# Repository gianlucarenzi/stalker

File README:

README
------

This adapter can be used in the same time with an internal Amiga Keyboard
-------------------------------------------------------------------------

1- The reset key-combo are:
   LCTRL - LAMIGA - RAMIGA
   LCTRL - LALT   - DELETE

More can be used on demand.
--------------------------

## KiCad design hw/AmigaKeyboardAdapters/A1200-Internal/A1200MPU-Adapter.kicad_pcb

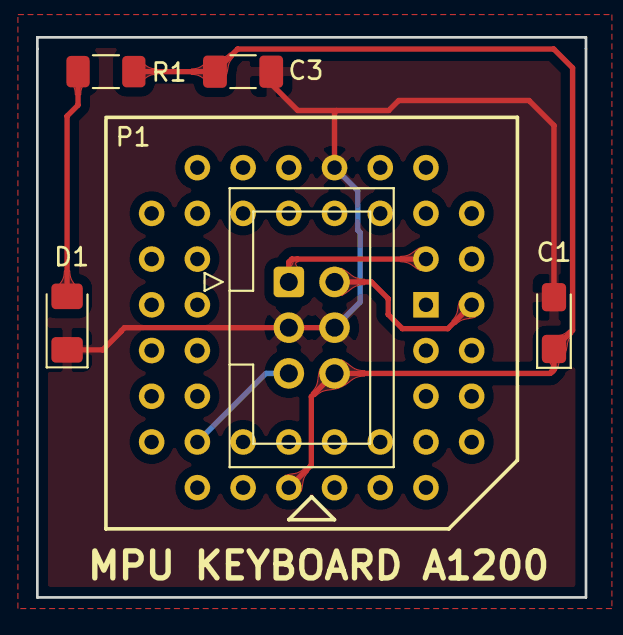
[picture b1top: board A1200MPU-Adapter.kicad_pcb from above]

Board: 2 copper layers, 30.5 x 31.1 mm, 6 parts (1 on the bottom side), 6 nets.

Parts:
C1: 10uF; CP_EIA-3216-12_Kemet-S_Pad1.58x1.35mm_HandSolder
C3: 100nF; C_1206_3216Metric_Pad1.33x1.80mm_HandSolder
D1: RED; LED_1206_3216Metric_Pad1.42x1.75mm_HandSolder
P1: Conn_02x03_Odd_Even; IDC-Header_2x03_P2.54mm_Vertical
R1: 330R; R_1206_3216Metric_Pad1.30x1.75mm_HandSolder
U1: A1200U13_REV_PLCC44; PLCC-44_THT-Socket_3D

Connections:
GND: C1.2, C3.2, D1.1, P1.3, P1.4, U1.35
unnamed: D1.2, R1.1
VCC5V: C1.1, C3.1, P1.6, R1.2, U1.13
mKBD_CLOCK: P1.1, U1.43
mKBD_DATA: P1.2, U1.44
mKBD_RESET: P1.5, U1.19

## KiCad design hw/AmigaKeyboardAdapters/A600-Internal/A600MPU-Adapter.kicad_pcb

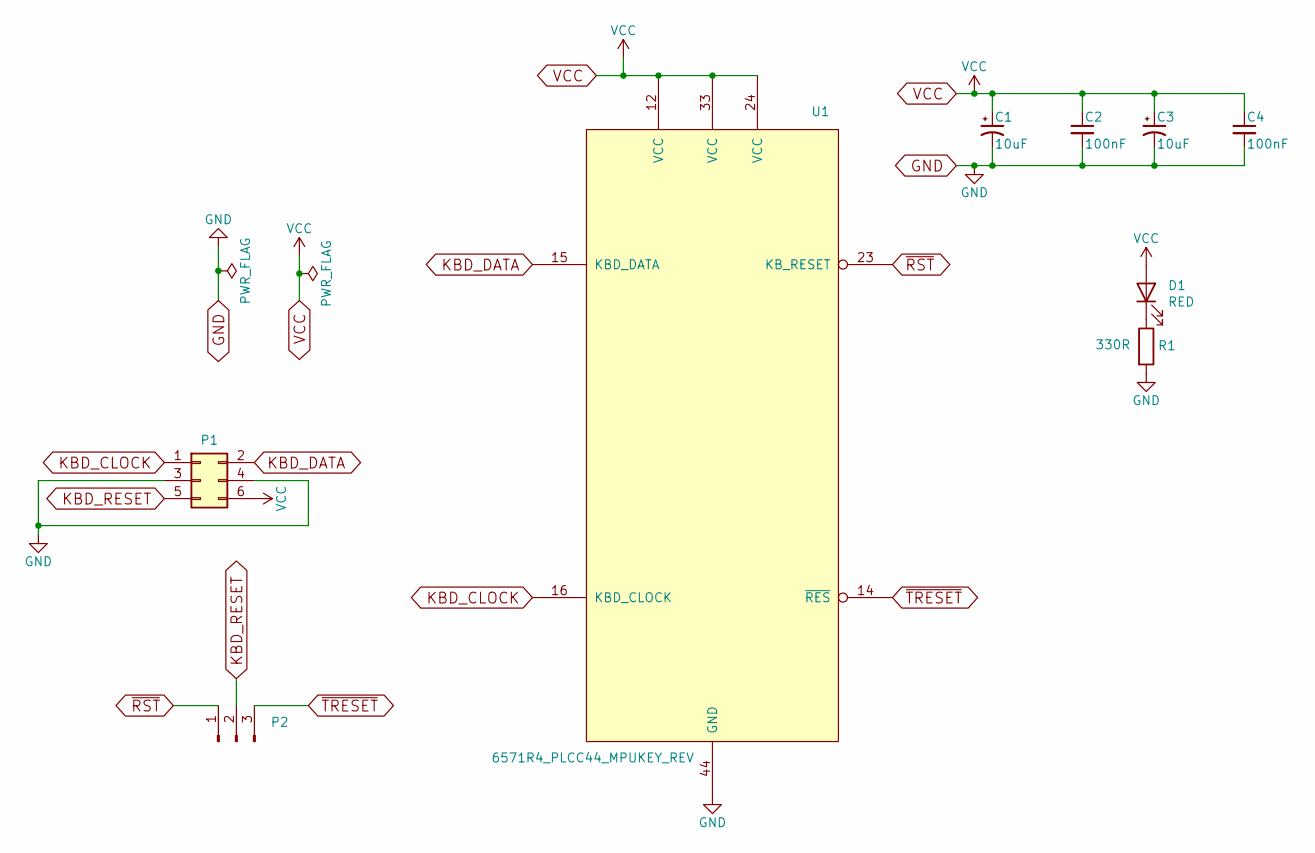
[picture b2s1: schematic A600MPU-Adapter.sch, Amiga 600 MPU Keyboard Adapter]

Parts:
C1, C3: 10uF; CP_EIA-3216-12_Kemet-S_Pad1.58x1.35mm_HandSolder; LCSC C108529
C2, C4: 100nF; C_1206_3216Metric_Pad1.33x1.80mm_HandSolder; LCSC C24497
D1: RED; LED_1206_3216Metric_Pad1.42x1.75mm_HandSolder; LCSC C93133
P1: Conn_02x03_Odd_Even; IDC-Header_2x03_P2.54mm_Vertical
P2: Conn_01x03_Male; PinHeader_1x03_P2.54mm_Vertical
R1: 330R; R_1206_3216Metric_Pad1.30x1.75mm_HandSolder; LCSC C245520
U1: 6571R4_PLCC44_MPUKEY_REV; PLCC-44_THT-Socket_3D

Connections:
GND: C1.2, C2.2, C3.2, C4.2, P1.3, P1.4, R1.2, U1.44 (GND)
KBD_CLOCK: P1.1, U1.16 (KBD_CLOCK)
KBD_DATA: P1.2, U1.15 (KBD_DATA)
KBD_RESET: P1.5, P2.2
unnamed: D1.1 (K), R1.1
VCC: C1.1, C2.1, C3.1, C4.1, D1.2 (A), P1.6, U1.12 (VCC), U1.24 (VCC), U1.33 (VCC)
~RST: P2.1, U1.23 (KB_RESET)
~TRESET: P2.3, U1.14 (~RES)

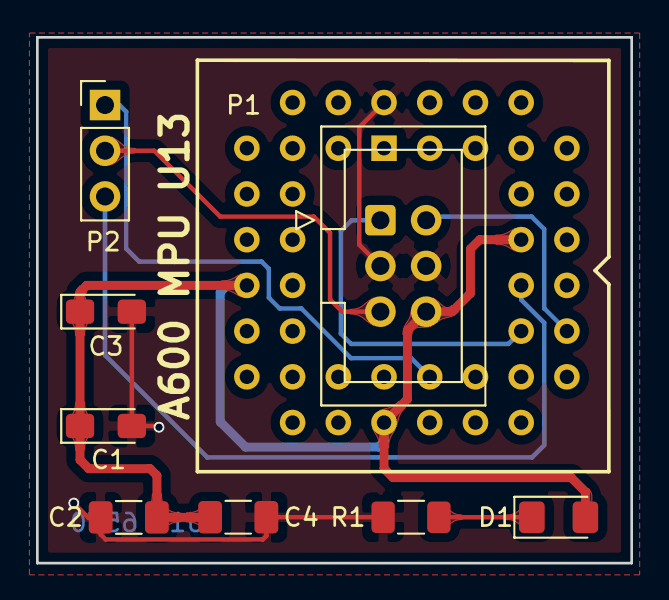
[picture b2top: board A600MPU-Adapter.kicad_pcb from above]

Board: 2 copper layers, 33.0 x 29.2 mm, 9 parts (1 on the bottom side), 8 nets.

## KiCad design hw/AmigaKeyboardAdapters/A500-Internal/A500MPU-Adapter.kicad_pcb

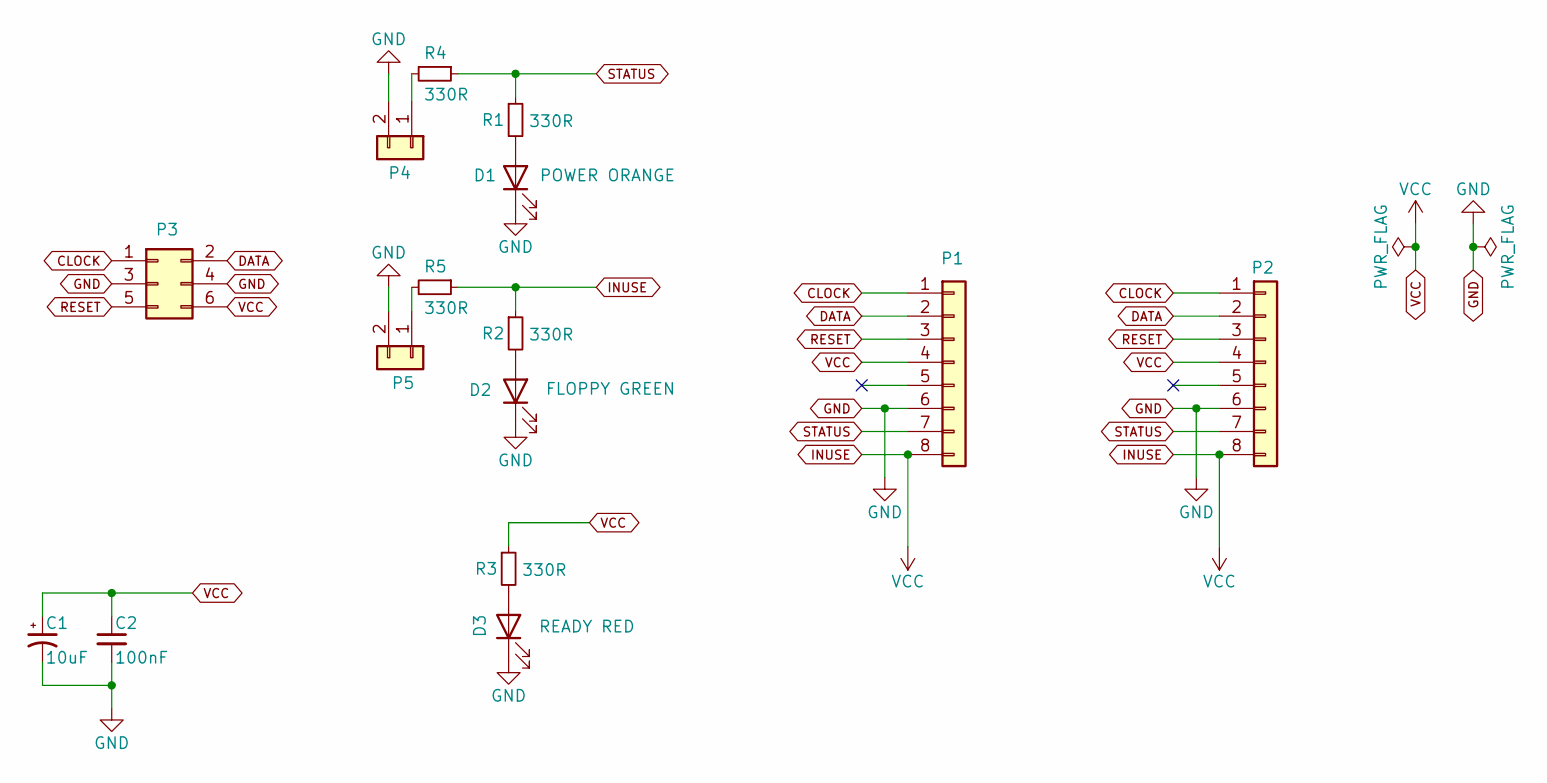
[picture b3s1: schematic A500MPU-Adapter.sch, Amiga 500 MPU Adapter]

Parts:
C1: 10uF; CP_EIA-3216-12_Kemet-S_Pad1.58x1.35mm_HandSolder; LCSC C108529
C2: 100nF; C_1206_3216Metric_Pad1.33x1.80mm_HandSolder; LCSC C24497
D1: POWER ORANGE; LED_1206_3216Metric_Pad1.42x1.75mm_HandSolder; LCSC C183851
D2: FLOPPY GREEN; LED_1206_3216Metric_Pad1.42x1.75mm_HandSolder; LCSC C2980185
D3: READY RED; LED_1206_3216Metric_Pad1.42x1.75mm_HandSolder; LCSC C93133
P1: Conn_01x08; PinHeader_1x08_P2.54mm_Vertical
P2: Conn_01x08; PinSocket_1x08_P2.54mm_Vertical
P3: Conn_02x03; IDC-Header_2x03_P2.54mm_Vertical
P4, P5: Conn_01x02; PinHeader_1x02_P2.54mm_Vertical
R1, R2, R3, R4, R5: 330R; R_1206_3216Metric_Pad1.30x1.75mm_HandSolder; LCSC C245520

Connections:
CLOCK: P1.1, P2.1, P3.1
DATA: P1.2, P2.2, P3.2
GND: C1.2, C2.2, D1.1 (K), D2.1 (K), D3.1 (K), P1.6, P2.6, P3.3, P3.4, P4.2, P5.2
INUSE: C1.1, C2.1, P1.4, P1.8, P2.4, P2.8, P3.6, R2.1, R3.1, R5.1
unnamed: D1.2 (A), R1.2
unnamed: D2.2 (A), R2.2
unnamed: D3.2 (A), R3.2
unnamed: P4.1, R4.2
unnamed: P5.1, R5.2
RESET: P1.3, P2.3, P3.5
STATUS: P1.7, P2.7, R1.1, R4.1

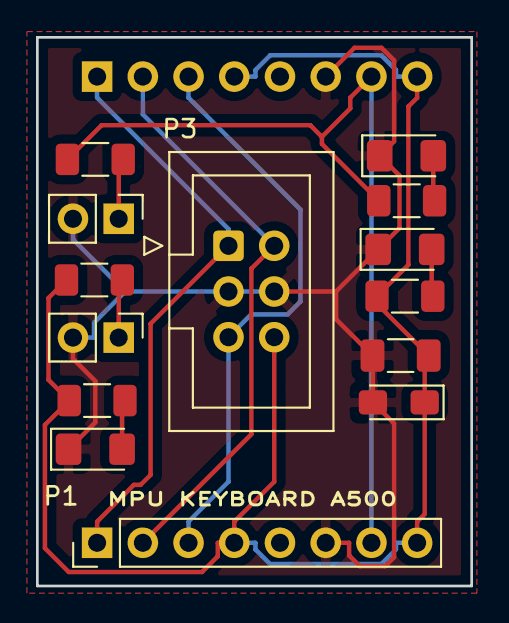
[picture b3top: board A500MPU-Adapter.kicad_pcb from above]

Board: 2 copper layers, 24.1 x 30.5 mm, 15 parts (1 on the bottom side), 11 nets.

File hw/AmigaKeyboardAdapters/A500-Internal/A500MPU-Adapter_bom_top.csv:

"Comment","Designator","Footprint","LCSC Part #"
"330R","R2 R3 R1 R4 R5","","C245520"
"100nF","C2","","C24497"
"10uF","C1","","C108529"
"Conn_02x03","P3","",""
"Conn_01x08","P1","",""
"Conn_01x02","P4 P5","",""
"FLOPPY GREEN","D2","","C2980185"
"READY RED","D3","","C93133"
"POWER ORANGE","D1","","C183851"

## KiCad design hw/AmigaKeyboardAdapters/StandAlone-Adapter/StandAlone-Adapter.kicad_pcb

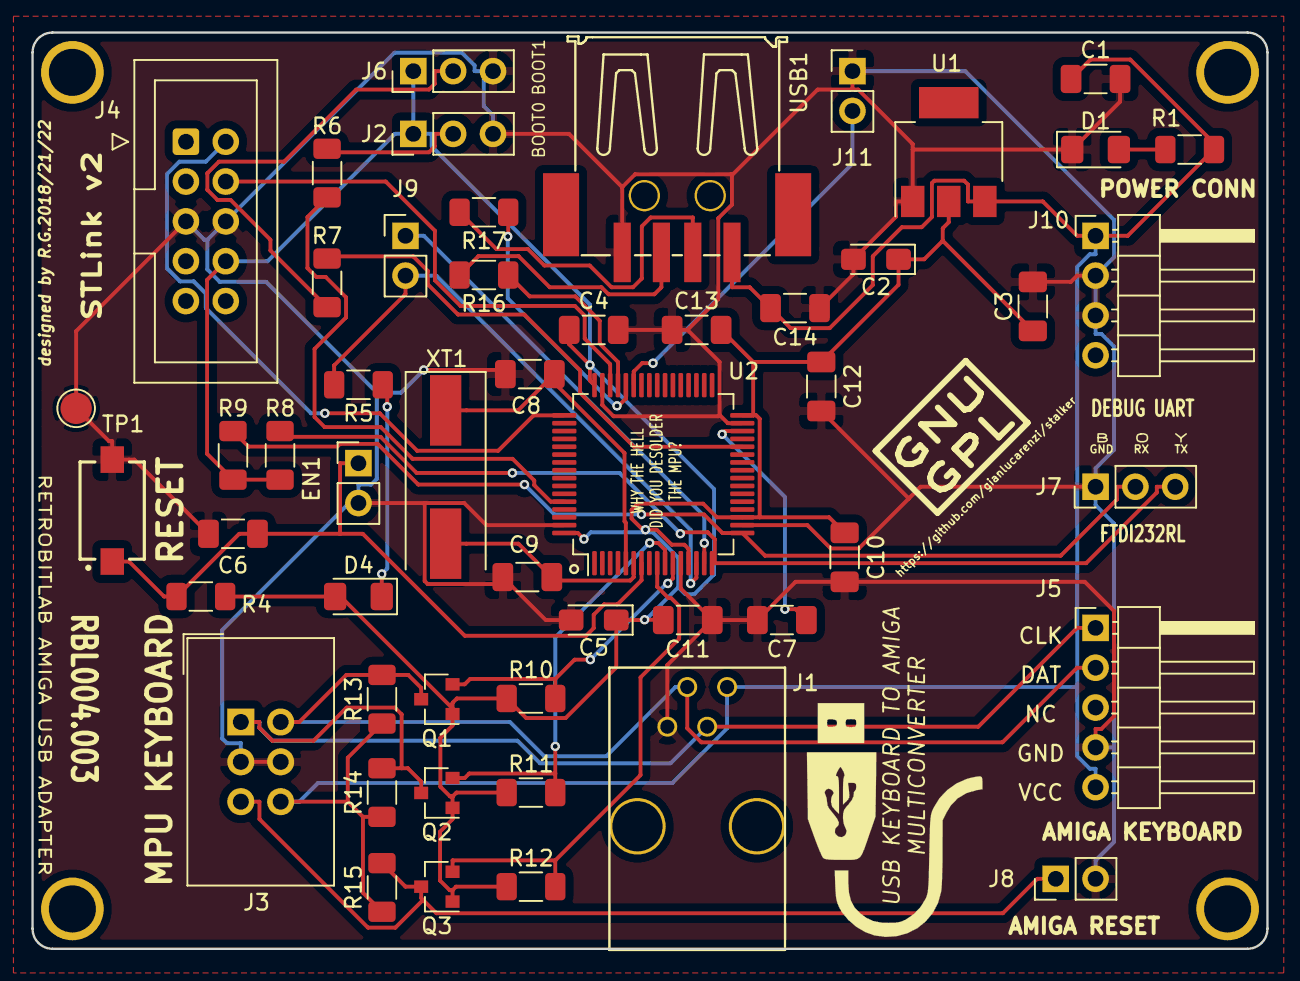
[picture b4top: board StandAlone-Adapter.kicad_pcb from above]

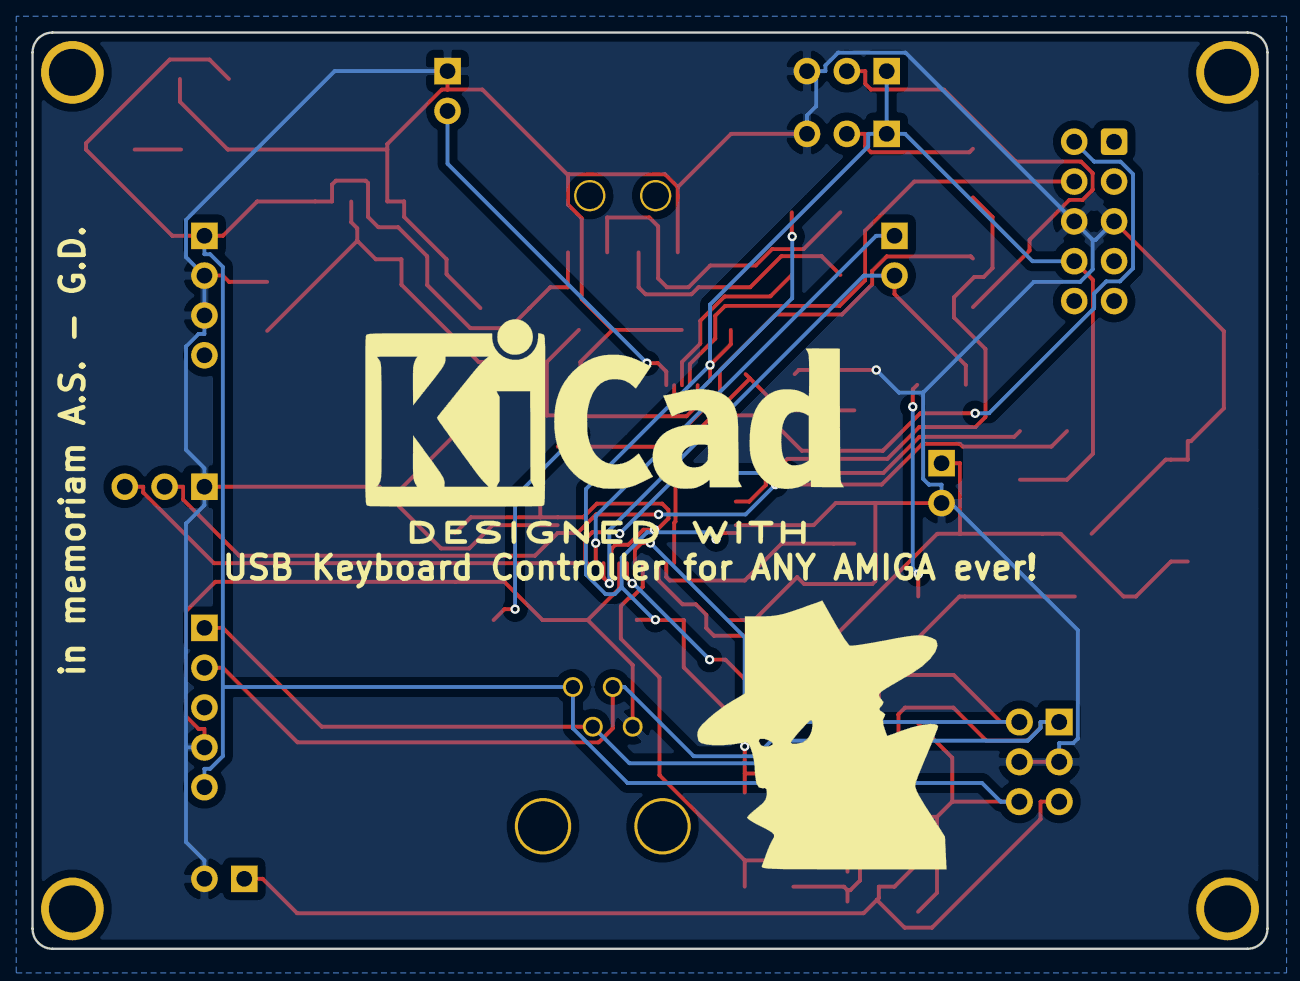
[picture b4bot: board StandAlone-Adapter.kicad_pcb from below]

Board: 2 copper layers, 78.7 x 58.4 mm, 60 parts (2 on the bottom side), 30 nets.

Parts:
C1: 100nF; C_1206_3216Metric_Pad1.33x1.80mm_HandSolder
C2: 10uF; CP_EIA-3216-12_Kemet-S_Pad1.58x1.35mm_HandSolder
C3, C4, C6, C10, C11, C12, C13, C14: 100n; C_1206_3216Metric_Pad1.33x1.80mm_HandSolder
C5: 10u; CP_EIA-3216-18_Kemet-A_Pad1.58x1.35mm_HandSolder
C7: 4.7uF; C_1206_3216Metric_Pad1.33x1.80mm_HandSolder
C8, C9: 22pF; C_1206_3216Metric_Pad1.33x1.80mm_HandSolder
D1, D4: RED; LED_1206_3216Metric_Pad1.42x1.75mm_HandSolder
EN1: CONN_01X02; PinHeader_1x02_P2.54mm_Vertical
H1, H2, H3, H4: CONN_01X01; MountingHole
J1: RJ10; RJ10-RECEPTACLE-Assmann-ASS-2004-3-4-LP-N-R
J2, J6, J7: Conn_01x03; PinHeader_1x03_P2.54mm_Vertical
J3: Conn_02x03_Odd_Even; IDC-Header_2x03_P2.54mm_Vertical
J4: JTAG SWDIO SWCLK; IDC-Header_2x05_P2.54mm_Vertical
J5: Conn_01x05; PinHeader_1x05_P2.54mm_Horizontal
J8, J9, J11: Conn_01x02; PinHeader_1x02_P2.54mm_Vertical
J10: Conn_01x04; PinHeader_1x04_P2.54mm_Horizontal
LOGO1: USB; USB_PLUG_15x15mm
LOGO2: GPL; KiCad-Logo2_12mm_SilkScreen
LOGO3: STALKER!; Symbol_GNU-GPL_SilkScreen_Small
LOGO4: Stalker Logo; Stalker_16.1x17.3mm
Q1, Q2, Q3: BSS138; SOT-23
R1, R5: 330R; R_1206_3216Metric_Pad1.30x1.75mm_HandSolder
R4, R6, R7, R8, R9, R10, R11, R12, R13, R14, R15: 10K; R_1206_3216Metric_Pad1.30x1.75mm_HandSolder
R16, R17: 22R; R_1206_3216Metric_Pad1.30x1.75mm_HandSolder
RESET1: SW_PUSH; SPST-7.3x3.9x2.5-WUERTH-434121025816
TP1: GND; TestPoint_Pad_D2.0mm
U1: AZ1117-3.3; SOT-223
U2: STM32F401RBTx; LQFP-64_10x10mm_P0.5mm
USB1: USB_A_SMD_LCSC; USB_A_M04P-F000_LCSC_C386738
XT1: 8Mhz; Crystal_SMD_HC49-SD

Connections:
+5V: C1.1, C14.2, J1.1, J3.6, J5.5, J10.1, R1.1, R13.1, R14.1, R15.1, U1.3, USB1.1
BOOT0: J2.2, R6.2
BOOT1: J6.2, R7.1
GND: C1.2, C2.2, C3.2, C4.2, C5.2, C6.1, C7.2, C8.2, C9.2, C10.1, C11.1, C12.1, C13.1, C14.1, D1.1, EN1.2, J1.4, J2.3, J3.3, J3.4, J4.5, J4.6, J5.4, J6.3, J7.1, J8.2, J10.2, J10.3, J11.1, RESET1.2, TP1.1, U1.1, U2.12, U2.18, U2.31, U2.47, U2.63, USB1.4
KBD_3v3_CLOCK: Q2.2, R11.2, U2.10
KBD_3v3_DATA: Q1.2, R10.2, U2.11
KBD_3v3_RESET: Q3.2, R12.2, U2.9
KBD_CLOCK: J1.2, J3.1, J5.1, Q2.3, R14.2
KBD_DATA: J1.3, J3.2, J5.2, Q1.3, R13.2
KBD_RESET: J3.5, J8.1, Q3.3, R15.2
NRST: C6.2, EN1.1, R4.1, RESET1.1, U2.7
unnamed: C7.1, U2.30
unnamed: C8.1, U2.5, XT1.1
unnamed: C9.1, U2.6, XT1.2
unnamed: D1.2, R1.2
unnamed: D4.1, R5.1
unnamed: R6.1, U2.60
unnamed: R7.2, U2.28
unnamed: R16.2, USB1.3
unnamed: R17.2, USB1.2
SWDCLK: J4.2, U2.49
SWDIO: J4.4, U2.46
TP1: J9.2, R5.2, U2.14
TP2: J9.1, U2.15
UART_RX_TTL: J7.2, R9.2, U2.17
UART_TX_TTL: J7.3, R8.2, U2.16
USB_ID: J11.2, U2.43
USB_N: R17.1, U2.44
USB_P: R16.1, U2.45
VCC3V3: C2.1, C3.1, C4.1, C5.1, C10.2, C11.2, C12.2, C13.2, D4.2, J2.1, J4.8, J6.1, Q1.1, Q2.1, Q3.1, R4.2, R8.1, R9.1, R10.1, R11.1, R12.1, U1.2, U2.13, U2.19, U2.32, U2.48, U2.64

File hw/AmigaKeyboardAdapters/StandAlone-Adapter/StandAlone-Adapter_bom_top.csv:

"Id";"Designator";"Package";"Quantity";"Designation";"Supplier and ref";
1;"C2";"CP_EIA-3216-12_Kemet-S_Pad1.58x1.35mm_HandSolder";1;"10uF";;;
2;"C3,C4,C6,C10,C11,C12,C13,C14";"C_1206_3216Metric_Pad1.33x1.80mm_HandSolder";8;"100n";;;
3;"C5";"CP_EIA-3216-18_Kemet-A_Pad1.58x1.35mm_HandSolder";1;"10u";;;
4;"C7";"C_1206_3216Metric_Pad1.33x1.80mm_HandSolder";1;"4.7uF";;;
5;"C8,C9";"C_1206_3216Metric_Pad1.33x1.80mm_HandSolder";2;"22pF";;;
6;"D1,D4";"LED_1206_3216Metric_Pad1.42x1.75mm_HandSolder";2;"RED";;;
7;"EN1";"PinHeader_1x02_P2.54mm_Vertical";1;"CONN_01X02";;;
8;"H1,H2,H3,H4";"MountingHole";4;"CONN_01X01";;;
9;"J1";"RJ10-RECEPTACLE-Assmann-ASS-2004-3-4-LP-N-R";1;"RJ10";;;
10;"J2,J6,J7";"PinHeader_1x03_P2.54mm_Vertical";3;"Conn_01x03";;;
11;"J3";"IDC-Header_2x03_P2.54mm_Vertical";1;"Conn_02x03_Odd_Even";;;
12;"J4,J10";"PinHeader_1x04_P2.54mm_Horizontal";2;"Conn_01x04";;;
13;"J5";"PinHeader_1x05_P2.54mm_Horizontal";1;"Conn_01x05";;;
14;"J8,J9,J11";"PinHeader_1x02_P2.54mm_Vertical";3;"Conn_01x02";;;
15;"Q1,Q2,Q3";"SOT-23";3;"BSS138";;;
16;"R1,R5";"R_1206_3216Metric_Pad1.30x1.75mm_HandSolder";2;"330R";;;
17;"R4,R6,R7,R8,R9,R10,R11,R12,R13,R14,R15";"R_1206_3216Metric_Pad1.30x1.75mm_HandSolder";11;"10K";;;
18;"R16,R17";"R_1206_3216Metric_Pad1.30x1.75mm_HandSolder";2;"22R";;;
19;"TP1";"TestPoint_Pad_D2.0mm";1;"GND";;;
20;"U1";"SOT-223";1;"AZ1117-3.3";;;
21;"U2";"LQFP-64_10x10mm_P0.5mm";1;"STM32F401RBTx";;;
22;"LOGO1";"USB_PLUG_15x15mm";1;"USB";;;
23;"LOGO2";"KiCad-Logo2_12mm_SilkScreen";1;"GPL";;;
24;"LOGO3";"Symbol_GNU-GPL_SilkScreen_Small";1;"STALKER!";;;
25;"LOGO4";"Stalker_16.1x17.3mm";1;"Stalker Logo";;;
26;"C1";"C_1206_3216Metric_Pad1.33x1.80mm_HandSolder";1;"100nF";;;
27;"RESET1";"SPST-7.3x3.9x2.5-WUERTH-434121025816";1;"SW_PUSH";;;
28;"XT1";"Crystal_SMD_HC49-SD";1;"8Mhz";;;
29;"USB1";"USB_A_M04P-F000_LCSC_C386738";1;"USB_A_SMD_LCSC";;;

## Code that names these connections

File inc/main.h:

/* USER CODE BEGIN Header */
/**
  ******************************************************************************
  * @file           : main.h
  * @brief          : Header for main.c file.
  *                   This file contains the common defines of the application.
  ******************************************************************************
  * @attention
  *
  * Copyright (c) 2025 STMicroelectronics.
  * All rights reserved.
  *
  * This software is licensed under terms that can be found in the LICENSE file
  * in the root directory of this software component.
  * If no LICENSE file comes with this software, it is provided AS-IS.
  *
  ******************************************************************************
  */
/* USER CODE END Header */

/* Define to prevent recursive inclusion -------------------------------------*/
#ifndef __MAIN_H
#define __MAIN_H

#define KBD_CLOCK_Pin       GPIO_PIN_2
#define KBD_CLOCK_GPIO_Port GPIOC
#define KBD_DATA_Pin        GPIO_PIN_3
#define KBD_DATA_GPIO_Port  GPIOC
#define KBD_RESET_Pin       GPIO_PIN_1
#define KBD_RESET_GPIO_Port GPIOC
#define TP1_Pin             GPIO_PIN_0
#define TP1_GPIO_Port       GPIOA
#define TP2_Pin             GPIO_PIN_1
#define TP2_GPIO_Port       GPIOA
#define LED_PIN_Pin         TP1_Pin
#define LED_PIN_GPIO_Port   TP1_GPIO_Port
#define DEBUG_TX_Pin        GPIO_PIN_2
#define DEBUG_TX_GPIO_Port  GPIOA
#define DEBUG_RX_Pin        GPIO_PIN_3
#define DEBUG_RX_GPIO_Port  GPIOA
#define USB_DM_Pin          GPIO_PIN_11
#define USB_DM_GPIO_Port    GPIOA
#define USB_DP_Pin          GPIO_PIN_12
#define USB_DP_GPIO_Port    GPIOA
#define USBH_Port           GPIOA

#ifdef __cplusplus
extern "C" {
#endif

/* Includes ------------------------------------------------------------------*/
#include "stm32f4xx_hal.h"

/* Private includes ----------------------------------------------------------*/
/* USER CODE BEGIN Includes */

/* USER CODE END Includes */

/* Exported types ------------------------------------------------------------*/
/* USER CODE BEGIN ET */

/* USER CODE END ET */

/* Exported constants --------------------------------------------------------*/
/* USER CODE BEGIN EC */

/* USER CODE END EC */

/* Exported macro ------------------------------------------------------------*/
/* USER CODE BEGIN EM */

/* USER CODE END EM */

/* Exported functions prototypes ---------------------------------------------*/
void Error_Handler(void);

/* USER CODE BEGIN EFP */

/* USER CODE END EFP */

/* Private defines -----------------------------------------------------------*/

/* USER CODE BEGIN Private defines */

/* USER CODE END Private defines */

#ifdef __cplusplus
}
#endif

#endif /* __MAIN_H */

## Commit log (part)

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2019-03-01 added the idc 2x3 box
2019-03-31 REfactoring for new Crystal Oscillator & new 1208 footprints handsoldering
2019-03-31 Bill Of Material Added
2019-03-31 Added Mouser's Bill of Material for 10 pcs. Just for reference for prices.
2019-04-01 Modified for better prices (10 pcs)
2019-04-05 removed. Must be reinstalled with the correctness of the files.
2019-04-12 Hide the LOGO label REF** on SilkScreen
2019-04-14 Modified for Capacitors & Added some boot options
    Replaced Electrolitic Capacitors with Tantalum ones. Added some
    capacitor as in the evaluation board schematics. Added BOOT1 pin. Added
    resistors for USB D+ D- lines. Increased the GND trace size to 0.35.
2019-04-18 Modified some logo and silkscreen stuff
2019-04-18 Added GNU GPL LOGO on silkscreen top
2019-04-18 Changed the capacitors for Crystal Oscillator. From 22pf to 20pf for 8Mhz
2019-04-22 Hide GNU LOGO Text
2019-06-05 Better optimization on release
2019-06-05 Better optimization on releaseAdded for gdb debug purposes
2019-06-17 Added the single-board Bill-Of-Material from DigiKey.
2019-06-17 Removed
2019-06-17 Removed unused Library (Memory Controller)
2019-06-22 KEYBOARD LED are in a binary format not decimal (each bit represent each led)
2019-06-22 Optimized even more (O3)
2019-06-22 Added SCROLL LOCK management
2019-06-22 Corrected. I do not have time to check what is really changed
2019-06-22 It works better with timed sync. Otherwise I have to rewrite the scan logic. BE CAREFUL: When using an internal keyboard and a USB keyboard, the logic with led for caps lock, scroll lock, and num loc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
2019-06-22 Rewrite of the lock mechanism. 1- The first press of a lock key (CAPS LOCK, NUM LOCK or SCROLL LOCK) send a _LOCK keycode to the system and lite up the corresponding led. 2- The following 'RELEASE' s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
    Works in Amiga 500 for now.
2019-06-22 Added check for reset when idle...
2019-06-22 Added a check for CLOCK line for external reset. 500msec of low means RESET!
2019-06-22 Corrected comment
2019-06-26 Updated silkscreen
2019-07-02 Changed comments to english
2019-09-07 Modified footprint of RJ10 (it was reversed)
2019-09-14 Revert "Modified footprint of RJ10 (it was reversed)"
    This reverts commit 65f5b3a9598e76c611fb4c453a8e3fe395b7212b.
2019-09-14 Added new images
2021-04-16 Modified for 128K as the STM32F401 with 128K is more common these days
2021-04-16 build folder is ignored
2021-04-16 From Kicad 4 to Kicad 5 update
2021-04-16 From Kicad 4 to Kicad 5
2022-05-25 Added DEBUG messages
2022-05-25 Added debug message
2022-10-13 Added a configuration for Amiga Reset. We can have a lot of Amiga reset keystrokes! LCTRL + LAMIGA + RAMIGA (standard) [ LGUI + RGUI ] LCTRL + LALT + RALT LCRTL + LALT + DEL (PC Standard) LCTRL + RAL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
2022-11-02 Removed Amiga (C)opyrighted stuff
2022-11-02 Rigenerated
2022-11-02 JLCPCB CPL
2022-11-04 Modifed project name
2022-11-04 Updated table for USB SCANCODES to AMIGA SCANCODES using: https://wiki.amigaos.net/wiki/Keymap_Library Added LCTRL for RESET checking
2022-11-05 Added 3D object for mechanical design
2022-11-07 Updated table. Added all Control keys (left and right)
2022-11-07 All components are SMD for a easier PCB production (LCSC and others) The jumper headers are optionals, so it will be soldered if needed. The programming tool STLINK_V2 will have a special programming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
2022-11-08 Done with bom2grouped_csv_jlcpcb.xsl
2022-11-08 Done by KiJLC plugin of PCBNEW
2022-11-08 MacOS ignore files
2022-11-09 Downloaded from LCSC
2022-11-09 Modified the JTAG STLinkV2 programmer port & SMT USB Type A connector
2022-11-10 For Autogeneration Routing (Kicad 5)
2022-11-10 For JLCPCB and LCSC Production
2022-11-10 Ignore cache lib files
2022-11-11 Updated to latest version (SMT - JLCPCB & LCSC Production run)
2022-11-14 First import. Must be adapted
2022-11-15 Added comments and swap tabs with spaces
2022-11-16 First try to autoproduce the bootloader
2022-11-16 No usb in this bootloader (it will be done in DFU)
2022-11-16 Modified for usage of only UART, GPIO. No more USB (it will be used inside the DFU mode)
2022-11-16 Ignore bootloader's build
2022-11-17 Sanity check added.
2022-11-29 Updated PWR_FLAGs
2022-11-29 New rendered images
2022-11-29 Updated PWR_FLAGs and other symbols
2022-11-30 Gerber for JLCPCB/PCBWay Production run
2022-11-30 Generated
2022-11-30 Generated for TOP & BOTTOM placement
2022-12-07 Smaller D1 silkscreen reference
2023-01-21 less verbose
2023-01-22 Removed unused macro
2023-01-22 Now flash.sh can be used to flash every firmware needed
2023-01-22 The application flash address space starts 0x4000 (16K) ahead of the bootloader, so the maximum amount of flash for application decrease from 128K to 112K
2023-01-22 Added NOISY output for debugging purposes
2023-02-11 Updated for a delayed USB init
2023-02-11 The SCB->VTOR has to be adapted for bootloader
2023-02-11 Adapter for bootloader (now 32K)
2023-02-11 First run
2023-02-11 Not needed but it is better to have
2023-02-13 Reduced Bootloader size to (hopefully) 16K
2023-02-13 Better calculation for size and start address
2023-02-15 Official release v1.2. Compiled without __EASTER_EGG__
2023-02-15 Modified RCC HSE setup as the CubeMX seems to have a bug, when calculating the clock resources the very first time. Change some of the divisors and resolve-the-issue works. :-/ It (should) works with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
    dfu-util --download build/stm32f401-usb-keyboard-amiga.bin --alt 0 --dfuse-address 0x08004000
    If does not work, change --alt 0 up to the numbers the system will gives you when invoking with --list option.
2023-02-18 Usage of the __appflash_start address (defined by the GNU linker script)
2023-02-18 Definition of the __appflash_start address for Application Start Address defined in the GNU linker script
2023-02-18 Change the linkerscript and the SCB->VTOR setting using the __appflash_start variable defined in the GNU linker script
2023-02-18 Usage of the __bootflash_start address (defined by the GNU linker script)
2023-02-18 Added #define DEBUG on DEBUG compiling: make DEBUG=1
2023-02-18 /* Prototypes */
2023-02-18 Added all symbols defined by the GNU linker script
2023-02-18 FWVER: v1.3 BUILD: 15:15:43-Feb 18 2023
2023-02-18 FWVER: v0.3 BUILD: 15:14:09-Feb 18 2023
2023-02-19 Updated year
2023-02-19 Eye Candy
2023-02-24 added PLCC-44
2024-01-16 Scripts for production
2024-01-16 The flash.sh command now flash only the application in hex format.
2024-01-16 All Aliexpress links will be opened in a new tab of the browser
2024-01-16 Update README.md
    Those tags are not working...
2024-01-17 When compiled with EASTER_EGG=yes it gives keystrokes in the Amiga OS.
2024-01-17 Added more ANSI Colors
2024-01-17 Keystrokes for Amiga OS are available only if EASTER_EGG=yes during make build. make EASTER_EGG=yes
2025-09-15 Added files for FreeRTOS
2025-09-15 Updated files for FreeRTOS
2025-09-15 target name fixed
2025-09-15 Two FreeRTOS task. Different vTaskDelay()
2025-09-15 heap reduced by half
2025-09-15 Alloc'd stack/heap up to 2K (512 words)
2025-09-16 Modified. All calls to amikb_* should be done in the amigaKeyboardTask within a STATE MACHINE. It should be simpler than having 3 or more specific xQueues.
2025-09-22 Commented out the Handlers used in FreeRTOS
2025-09-22 Added Doxygen comments
2025-09-22 FlowChart
2025-09-22 TAB instead of spaces
2025-09-22 DBG_W() added
2025-09-22 Optimized code
2025-09-22 Semplified as the timing is in the caller's code.
2025-09-22 Spaces to TABs
2025-09-22 FW1.5-RTOS
2025-10-08 Safe Priority for FreeRTOS and Watchdog from bootloader (if any)
2025-10-08 Disable Watchdog Interrupt WWDG as soon as possible
2025-10-08 This means that my previous change to set USE_RTOS to 1, although logically correct for an RTOS project, is incompatible with this version of the library. The other changes, particularly lowering the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
2025-10-11 demo FreeRTOS runs. Now port every working code into stalker main
2025-10-11 updated to ignore
2025-10-12 As in the demoFreeRTOS (it's working)
2025-10-12 In the demo was at sysmem.c as the only function. We put it here
2025-10-12 as in demoFreeRTOS
2025-10-12 Priority levels as in demoFreeRTOS
2025-10-12 Application starts @ 16K
2025-10-12 Added some comments and spaces <---> tabs
2025-10-13 Removed. It should not be needed anymore
2025-10-13 V1.6-RTOS
2025-11-01 RetroBitLab library
2025-11-02 usb task need more stack and higher priority
2025-11-02 refactor from original main loop
2025-11-02 EEPROM emulation support
2025-11-02 On some keyboards we cannot have RGUI key. So we can use KEY_APPLICATION / KEY_COMPOSE
2025-11-04 Differenziamo tra le attese con OS e quelle senza. Nei task e' meglio usare quelle dell'OS ove possibile (mdelay), mentre si lasciano le udelay in quanto FreeRTOS ha una granularita' maggiore
2025-11-04 aggiunta modulo base per supporto HID esteso
2025-11-04 feat(hid): Implement bridge for extended HID to Amiga key combos
    This commit introduces a bridge to translate extended HID events (e.g., from consumer control devices) into standard Amiga key combinations. This allows the use of multimedia keys (Volume, Play/Pause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
    A new task, `extended_to_amiga_task`, reads HID usages from the `extended_input_queue`, maps them to `CTRL+ALT+Fn` sequences as defined in `HID_EXTENDED_MAPPING.md`, and injects them into the Amiga p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
    Key changes:
    **New Task (`extended_bridge.c`)**: Implements the bridge logic, including management of modifier (CTRL, ALT) reference counts to p
2025-11-04 Depending on saved configuration, the RESET will be invoked with: PC MODE: (L/R)CTRL + (L/R)ALT + DELETE AMIGA MODE: (L/R)CTRL + LGUI + RGUI (or APPLICATION if some of the (L/R)GUI is missing)
2025-11-04 LCTRL + LALT + LSHIFT + P: toggle configuration RESET. From AMIGA mode (CTRL-A-A) to PC mode (CTRL-ALT-DEL) This configuration is stored in EEPROM
2025-11-04 **Extended HID Support**: The firmware first attempts to operate in **Boot Protocol** for broader compatibility. If the Boot Protocol is not supported, it falls back to **Report Protocol**, allowing 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
2025-11-04 Added USB DEBUGGING
2025-11-05 Variables changed to volatile to set the optimization out of this code.
    Before the fix, you might see:
    - Keyboard never detected even when plugged in
    - LED stuck in "waiting" blink pattern
    - DBG_N("APPLICATION READY") prints, but code doesn't enter the handler
    After the fix:
    - Keyboard reliably detected
2025-11-05 Add defensive NULL checks for FreeRTOS queues at task startup
2025-11-05 Optimization for internal variables (compiler's wrong assumptions) and warning if there are available slots for more keys, so print a warning message (this keypress/release will be lost, anyway)
2025-11-05 Gestione corretta overflow 32bit dopo 49 giorni uptime (con timertick a 1ms)
2025-11-05 La variabile current_mode e' impostata a 'volatile' poiche' viene letta nel main ed utilizzata in piu' task. Nel task usb viene poi scritta in EEPROM e ricaricata.
2025-11-05 The shared variable usb_app_state type is changed to 'volatile' because of the nature's of the sharing. The compiler now cannot optimize it out
2025-11-05 Macro removed from the C code. Now it's on the header
2025-11-05 Include usbh_conf.h for USBH_USE_OS macro
2025-11-05 amikb_process() now it is aware of the usage of the FreeRTOS
2025-11-05 v2.0.5-rc-RTOS Release Candidate Build
2025-11-06 feat: Implementata emulazione EEPROM robusta con scrittura flash bufferizzata
    Questo commit risolve un problema per cui il microcontrollore si poteva bloccare durante le operazioni di scrittura della EEPROM, in particolare all'inizializzazione di una EEPROM non valida. La prec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
    Le modifiche principali includono:
    o Script del Linker (`stm32f401rctx_flash.ld`)
    Aggiornata la dimensione della flash a 256KB (STM32F401RC).
    Dedicato il FLASH_SECTOR_1 (16KB) all'emulazione EEPROM, isolandolo dal codice dell'applicazione.
    o Header EEPROM (`inc/eep
2025-11-06 v2.0.5-rc-RTOS
2025-11-06 no eeprom support
2025-11-06 Si compila
2025-11-07 OS Aware mdelay
2025-11-14 Rimossi
2025-11-16 Format flash
2025-11-16 Now production can be used even for building (build argument)
2025-11-16 Same clock sources
2025-11-16 Removed unused flags
2025-11-17 new image for downloading
2025-11-19 FWVER3.1-RTOS: added the possibility of receiving a KEY_HELP from a USB keyboard. This keyevent can be generated by a specific USB Keyboard if any.
2026-02-18 Added gitignore for A600 Adapter
2026-02-18 Old version
2026-02-18 V3 RBL007.002 - Corrected F.Silkscreen for MPU U13 6570. Thanks to Pietro Colombo for pointing that issue
2026-02-18 V3 RBL007.002 With TEARDROPS - Corrected F.Silkscreen for MPU U13 6570. Thanks to Pietro Colombo for pointing that issue
2026-02-19 Updated from Library. /IRQ is not tied at VCC anymore.
2026-02-19 Removed. Not needed anymore
2026-02-19 Updated the symbol and the positioning of the footprint in bottom layer. Now all signals are checked with PCBEXPLORER for A600 (June Bug version) They seem to be ok. Updated from library too.
